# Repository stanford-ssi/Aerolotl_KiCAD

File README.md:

# Aerolotl_KiCAD, make sure to only one person works on it at a time

## Boards in this repo

- Aerolotl SRAD flight computer: the KiCad project at the top level.
- [Battery PCB](BatteryPCB/README.md): the AV bay battery, arming and camera board, with its ordering BOM and Gerbers in `BatteryPCB/fab/`.

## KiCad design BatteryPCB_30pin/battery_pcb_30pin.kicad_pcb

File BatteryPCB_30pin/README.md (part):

# Battery PCB, 30-pin ESP32 version — AV bay power, arming and camera board

> **This folder is a copy of [`../BatteryPCB`](../BatteryPCB) made on 11 Oct 2026 for a 30-pin ESP32 DevKit V1**
> (DOIT layout, ESP-WROOM-32, 2 × 15 pins, rows 25.4 mm apart) instead of the 38-pin ESP32-DevKitC. Only the ESP32
> sockets and what connects to them changed: J1/J2 are 1×15 with pin 1 exactly where the DevKitC's was, the six used
> pins (5 V, GND, GPIO34, GPIO17, GPIO16, GPIO2) are re-routed, R7/R8 and C9/C10 moved next to their new pins,
> and the silk and antenna keep-out follow the new board. Same GPIOs, so the firmware is unchanged.
> See [`LAYOUT_NOTES.md`](LAYOUT_NOTES.md), "30-pin version".

The battery board for the SSI IREC AV bay: it holds the cells for both flight computers
(each with its own pin-switch arming plug) and a 2S pack that powers an ESP32 and a
RunCam Split 4 camera on the back. Formerly called CamControl.

Open `battery_pcb_30pin.kicad_pro` in KiCad 10. The board is a 5.72 in (145.3 mm) round, 2-layer disc
for the AV bay, placed and fully routed.

**Status (30-pin version, 11 Oct 2026):** ERC 0 errors · DRC 0 violations (warnings included) under the strict rules below, with full schematic parity
(3 documented exclusions, as on `BatteryPCB`; checked with KiCad 10.0.6, see `battery_pcb_30pin.kicad_dru`) · `tools/layoutA/verify_A.py` ALL PASS (36 checks; its cut-out check now counts the 7 rim
notches and Koichi's 4 square zip-tie cut-outs). Ready to order: see [Ordering](#ordering).
[`LAYOUT_NOTES.md`](LAYOUT_NOTES.md) has the history of every layout decision.

---

## What's on it

| Block | Parts |
|---|---|
| 2S pack for camera + ESP32 | BT1, BT2 in series → 7.4 V nom / 8.4 V max |
| Input protection | F1 2 A polyfuse → SW1 (camera power switch plug) → Q1 AO3407A reverse-polarity PMOS (gate to GND, ~0.05 V drop) → D1 SMBJ12A TVS |
| Buck 8.4 V → 5.0 V | U1 LMR51430 (500 kHz) + L1 6.8 µH + FB divider; input caps C1 100 nF (at U1's pins) + C2, C11 10 µF |
| Low-battery cut-off | R9 402k / R10 100k on U1's EN: on above 6.2 V, off below 5.4 V at VIN (about 2.7 V per cell), so the 2S pack is never run flat |
| 30-pin ESP32 DevKit V1 socket | J1, J2 — 2 × 1×15 female headers |
| Camera harness | J3 — JST GH 5-pin (+5V, GND, RX, TX, VIDEO), on the back |
| Camera mount | H7–H10 — four M2 × 5 mm SMT standoffs on a 25.5 mm square, on the back |
| Status LED | R6 + D2 on GPIO2 |
| Pack voltage telemetry | R4 100k / R5 39k divider + C8 → GPIO34 (`VBAT_SENSE = VIN × 39/139`, ≤ 2.36 V) |
| Test points | 2 mm through-hole pads, open on both sides. **Right-edge block** (front, between the right rod and the lower zip-tie cut-out, top row / bottom row): TP1 +5V / TP3 GND, TP5 COTS cell + / TP6 COTS cell −, TP7 SRAD cell + / TP8 SRAD cell −. **Lower left** by the camera switch: TP2 VBAT+ (2S pack, before the fuse) / TP4 GND |
| COTS supply | BT3 → SW2 (COTS pin switch plug) → J5 XT30 to the TeleMetrum |
| SRAD supply | BT4 → SW3 (SRAD pin switch plug) → J6 XT30 to the Aerolotl |

Harness connectors are latching Molex Micro-Fit 3.0 for the switch leads (SW1–SW3) and JST GH for the
camera (J3). The two battery outputs, J5 and J6, are **AMASS XT30** (male XT30UPB-M on the board):
**pin 1 is minus, pin 2 is plus**, as moulded on the housing and printed beside each one. The cables take an
XT30U-F female plug. The footprint retains its legacy XT30UPB-F name; order XT30UPB-M (C428721). XT30 holds by friction, so tape or tie the plugs for flight. The male pins are exposed and plus is live when its arming switch closes; keep the mating plug connected or cover the pins when armed.

---

## Three design decisions worth knowing

### 1. The Split 4 has no GPIO shutter line

Its harness is **VCC / GND / Video**. Recording start/stop is done over **UART**
using the RunCam Device Protocol on the TX/RX pads, not a single logic pin.

So the schematic wires **UART2** (GPIO17 TX, GPIO16 RX) to the camera through
series resistors: R7 100 Ω on the ESP32's TX, R8 1 kΩ on the camera's TX (so a 5 V camera
output can't push more than about 1 mA into GPIO16). UART0 is left free so you can still
program and debug over USB. On the original DOIT DevKit V1 design, VIN is fed from USB through an SS14 Schottky, so
USB and this board's 5 V can be connected at the same time. Clones vary: until you have checked yours (USB only:
VIN should read about 4.6–4.8 V, one diode drop below USB), switch the camera pack off before plugging USB in.

The camera connects to this board through the 5-pin J3 harness only (no
button-pad wiring).

**The camera harness is a straight cable.** The Split 4 has five solder pads, in this order with Side B
facing you: RX, TX, Video, GND, VCC. J3 is in the same order (pin 5 … pin 1), so each wire goes straight across,
no crossing (J3's pins 3 and 5 were swapped on 11 Oct 2026 to make this so):

| J3 pin | Net | Camera pad |
|---|---|---|
| 1 | +5V | VCC |
| 2 | GND | GND |
| 3 | VIDEO | Video, or leave unconnected (nothing on this board uses it) |
| 4 | CAM_TX (to ESP32 RX through R8) | TX |
| 5 | CAM_RX (ESP32 TX through R7) | RX |

Note: the original `BatteryPCB` still has the old order (3 = RX, 5 = Video), so its harness is wired by label.

### 2. Everything runs off one 5 V buck

The camera accepts 5–20 V, so 2S could feed it directly — but RunCam explicitly
warns to power it from a regulator rather than a raw battery bus.

Feeding the ESP32 8.4 V directly would also be a problem: the devkit's onboard
AMS1117 would drop 8.4 → 3.3 V and burn about **1.3 W** in a SOT-223. It would
run very hot.

One LMR51430 at 5 V solves both. The ESP32's regulator then only drops 5 → 3.3 V,
and the camera gets a clean supply.

Feedback divider: `Vout = 0.6 × (1 + 100k / 13k) = 5.22 V` (5.05–5.39 V worst case over resistor and reference tolerance, so the camera always sees ≥ 5.0 V)

### 3. COTS and SRAD grounds are deliberately isolated

`COTS_BAT-` and `SRAD_BAT-` are **not** tied to `GND`.

DTEG §6.9.1 requires completely independent recovery systems — separate power
supplies included. Tying the returns together would create a shared failure path
and defeat that. Each of those two cells is its own island: own cell, own switch,
own two-wire output.

Do not "clean this up" by merging the grounds.

---

## Which ESP32

A **30-pin ESP32 DevKit V1** with the DOIT pinout and a WROOM module (the team's USB-C / CP2102 board is one): 2 × 15 pins,
rows 1.0 in (25.4 mm) apart, header order EN, VP, VN, D34 … D13, GND, VIN on one side and D23, D22, TX0 … D15, GND, 3V3 on
the other (antenna at the top). The sockets are wired to that order pin for pin.

- **Check the row spacing before you solder the sockets:** 25.4 mm between the centres of two facing pins. A few narrow
  clones are 22.9 mm; they won't fit.
- **Not a WROVER module:** it uses GPIO16/17 for its PSRAM, and this board uses them for the camera UART.
- **Not the 38-pin ESP32-DevKitC:** that one needs `../BatteryPCB` (2 × 19 sockets).
- It plugs in from the **back**, components facing away from this board, antenna end toward the top: **EN** and **D23**
  go at the "ANTENNA END" silkscreen, **VIN** and **3V3** at the USB end (both labelled on the back silk).
- The board sits inside the area the DevKitC used (51.3 × 28 mm vs 54.3 × 27.9 mm), so nothing new is in its way. Its
  module doesn't overhang: the antenna ends about 5.4 mm past pin 1, about 1.9 mm further in than the DevKitC's.
- **Antenna clearance.** Espressif recommends at least 15 mm of clearance in every direction around the module's PCB
  antenna. The devkit hangs about 13.4 mm under this board, so the back copper has a keep-out (no pour, tracks or vias)
  15 mm to each side of the antenna and past its end, outlined on the back silk (extended 1.9 mm toward the centre for
  this board's antenna). Everything on the front, cells and pin-switch stack included, is at least 15 mm away through
  the board. **Use a nylon M3 bolt and nut in H5**: it is the pin-switch stack bolt right over the antenna.
  [Espressif: positioning a module on a base board](https://docs.espressif.com/projects/esp-hardware-design-guidelines/en/latest/esp32/pcb-layout-design.html#general-principles-of-pcb-layout-for-modules-positioning-a-module-on-a-base-board)
- The AVBay1 Onshape model already shows a 2 × 15 DevKit, which matches this version.

## ESP32 pin map

| Function | Pin | Net |
|---|---|---|
| 5 V in | J1-15 (VIN) | `+5V` |
| GND | J1-14, J2-14 | `GND` |
| Camera UART TX | J2-9 (TX2, GPIO17) | `ESP_TX2` → R7 → `CAM_RX` |
| Camera UART RX | J2-10 (RX2, GPIO16) | `ESP_RX2` → R8 → `CAM_TX` |
| Status LED | J2-12 (D2, GPIO2) | `LED_GPIO` → R6 → D2 |
| Pack voltage | J1-4 (D34, GPIO34, ADC1) | `VBAT_SENSE` |

J1 is the devkit's EN … VIN header and J2 its D23 … 3V3 header,
both counted from the **antenna end**, which faces the top of the board. Same GPIOs as the DevKitC version.

Every unused header pin is broken out to a named net (`L06_IO35`, `R09_IO18`, …)
so you can see what's free. Those produce 24 `isolated_pin_label` ERC warnings —
expected and harmless, they're spare breakouts by design.

The 30-pin board doesn't break out GPIO6–11 (the module's SPI flash) or GPIO0. Of the strapping pins it does break out,
keep GPIO12 (`L12_IO12`) low at boot; GPIO2 (the LED, pulled low through R6/D2) and GPIO15 are fine as wired.

---

## Camera mounting

The RunCam Split 4 board (29 × 29 mm, M2 holes on a 25.5 mm square) sits on four Würth
9774050243R M2 × 5 mm SMT standoffs (H7–H10) on the back of this board, next to its J3 harness.
Each standoff has a 1.4 mm locating pin on its base that drops into a 3.0 mm hole in the board (Würth's land pattern);
the pin stays inside the 1.6 mm board, so nothing reaches the battery side. Use M2 screws 4–6 mm long.
`battery_pcb.pretty/RunCam_Split4_OnStandoffs.kicad_mod` places its 3D outline; it has no pads
and is excluded from the BOM.

Source: [RunCam Split 4 manual](https://www.runcam.com/download/split4k/RC_Split_4k_Manual_EN.pdf)

---

## Open items

1. **The ESP32's Bluetooth is a 2.4 GHz transmitter.** DTEG §4.3.5 forbids
   powering transmitting electronics in the pit area without authorization, and
   2.4 GHz is not in ESRA's Student Band Plan. SW1 exists partly so you can keep
   it off until the pad. Declare this radio in your progress reports.
2. **No SD card module** is on this schematic — you mentioned one for the plate
   but didn't list it in the brief. Easy to add on SPI (GPIO5/18/19/23).
3. **Confirm the camera's logic level** before connecting RX/TX: power the camera and
   measure its TX pad to GND. About 3.3 V: wire it straight on. About 5 V: R8 (1 kΩ)
   protects the ESP32's input, but the camera may not read the ESP32's 3.3 V TX; add a
   level shifter then.

Layout-specific items are in [`LAYOUT_NOTES.md`](LAYOUT_NOTES.md).

---

## Mechanical dimensions

Front view (battery side), origin at the board centre, **x right, y up toward the pin-switch stack** (the Onshape frame).
All in mm unless noted.

| Feature | Size | Position |
|---|---|---|
| Board | Ø 145.29 (5.720 in), 1.6 thick FR-4 | centred |
| Rod holes H1/H2 (3/8 in threaded rod) | Ø 10.32 (13/32 in) | (−60, 0), (60, 0): 120 apart |
| Rod washer keep-out (no copper, both faces) | Ø 21.2 | around H1/H2 |
| TeleMetrum sled screw holes H3/H4 (M4) | Ø 4.5 | (−8.7, −50), (8.7, −50): 17.4 apart |
| Sled screw keep-out (no copper) | Ø 9.6 | around H3/H4 |
| Pin-switch stack bolt holes H5/H6 (M3) | Ø 3.2 | (18.5, 41.88), (−18.5, 48.88) |
| Pin-switch stack footprint (silk outline) | 45 wide, from y 36.88 out to the pin faces at 68.88 | x −22.5 … 22.5 |
| Camera standoffs H7–H10 (back, Würth M2 × 5 mm SMT) | 25.5 square | centre (−35.5, 30): upper left, near the rim |
| Battery holders BT1–BT4 (Keystone 1042) | 14.9 tall | centres x −36.5, −14.3, 11.1, 36.5; y −2.25 |
| ESP32 sockets J1/J2 (back, 1×15, 8.5 tall) | columns 25.4 apart | x 23.8 and −1.6; pin 1 at y 35.12, pin 15 at y −0.44 |
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
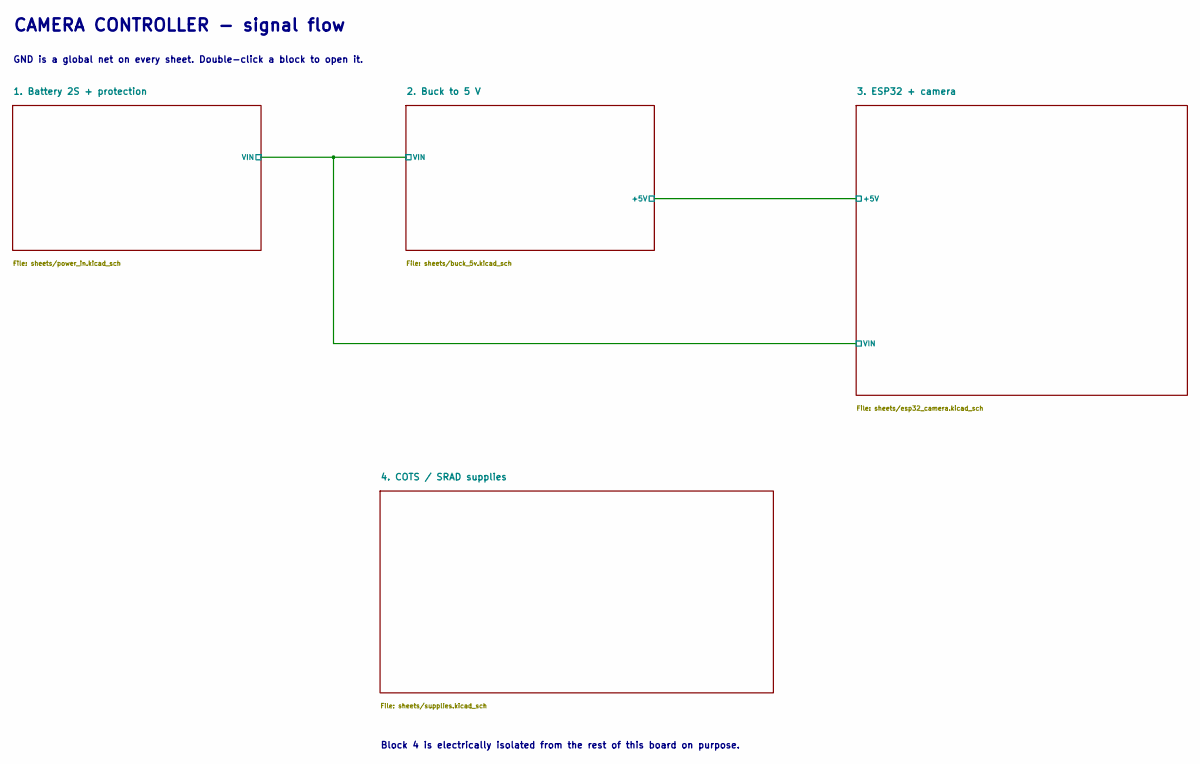
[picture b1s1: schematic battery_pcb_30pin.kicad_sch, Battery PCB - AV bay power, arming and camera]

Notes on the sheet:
CAMERA CONTROLLER - signal flow
GND is a global net on every sheet. Double-click a block to open it.
Block 4 is electrically isolated from the rest of this board on purpose.

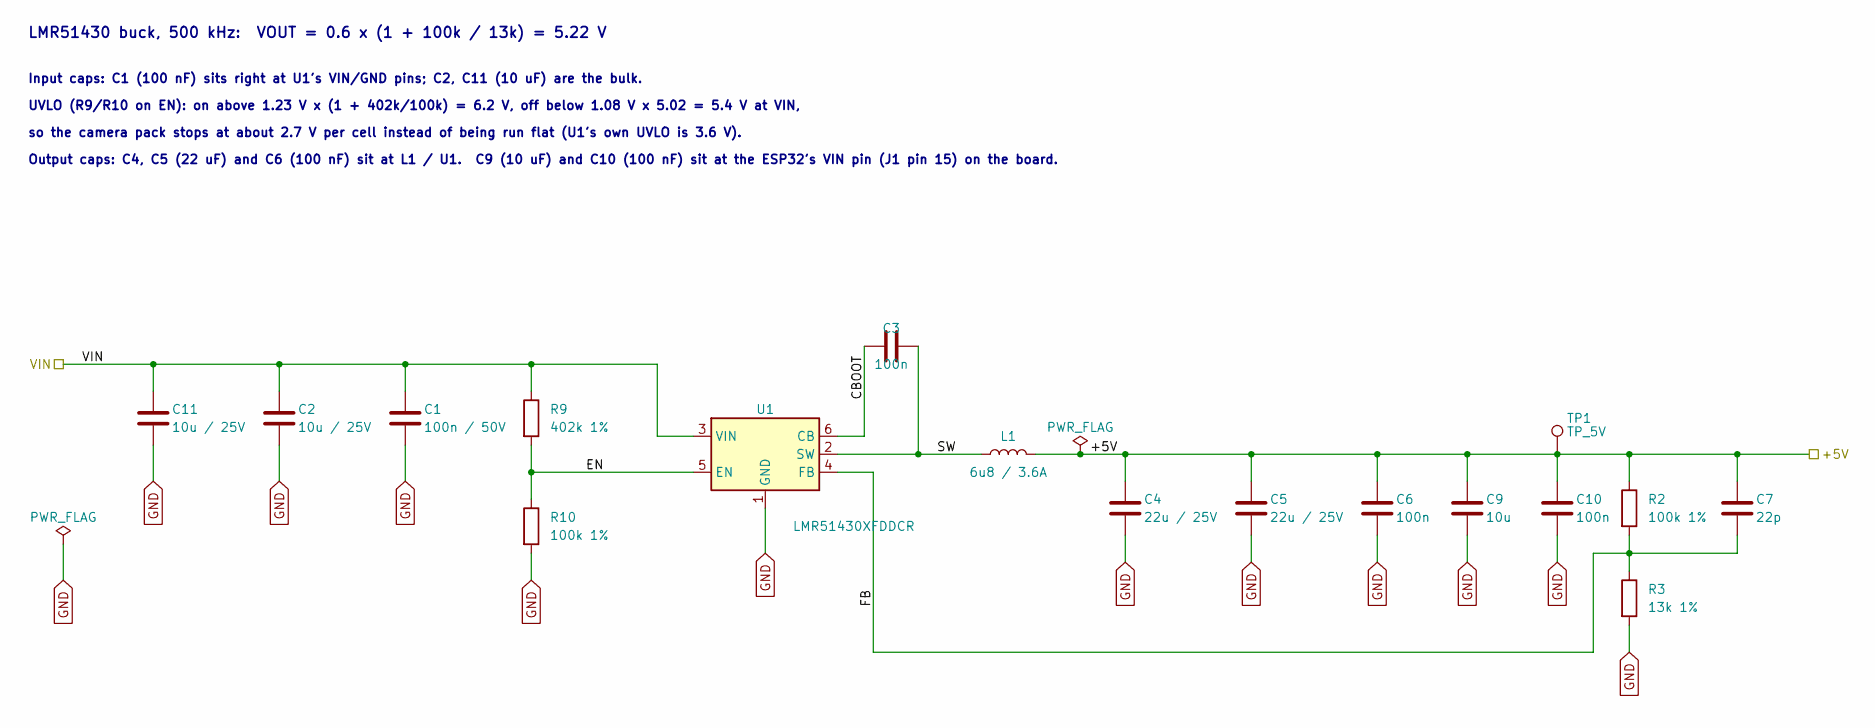
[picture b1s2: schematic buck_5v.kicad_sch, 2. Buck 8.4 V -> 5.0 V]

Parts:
C1: 100n / 50V; C_0805_2012Metric; MPN CC0805KRX7R9BB104; LCSC C49678
C2, C11: 10u / 25V; C_0805_2012Metric; MPN CL21A106KAYNNNE
C3, C6, C10: 100n; C_0603_1608Metric; MPN CL10B104KB8NNNC
C4, C5: 22u / 25V; C_0805_2012Metric; MPN CL21A226MAQNNNE; LCSC C45783
C7: 22p; C_0603_1608Metric; MPN CL10C220JB8NNNC
C9: 10u; C_0805_2012Metric; MPN CL21A106KAYNNNE
L1: 6u8 / 3.6A; L_Bourns_SRN6045TA; MPN SRN6045TA-6R8M
R2, R10: 100k 1%; R_0603_1608Metric; MPN RC0603FR-07100KL
R3: 13k 1%; R_0603_1608Metric; MPN RC0603FR-0713KL
R9: 402k 1%; R_0603_1608Metric; MPN RC0603FR-07402KL
TP1: TP_5V; TestPoint_THTPad_D2.0mm_Drill1.0mm
U1: LMR51430XFDDCR; SOT-23-6; MPN LMR51430XFDDCR

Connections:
/1. Battery 2S + protection/VIN: C1.1, C2.1, C11.1, R9.1, U1.3 (VIN); also elsewhere on the board
/2. Buck to 5 V/+5V: C4.1, C5.1, C6.1, C7.1, C9.1, C10.1, L1.2, R2.1, TP1.1 (1_1); also elsewhere on the board
/2. Buck to 5 V/CBOOT: C3.1, U1.6 (CB)
/2. Buck to 5 V/EN: R9.2, R10.1, U1.5 (EN)
/2. Buck to 5 V/FB: C7.2, R2.2, R3.1, U1.4 (FB)
/2. Buck to 5 V/SW: C3.2, L1.1, U1.2 (SW)
GND: C1.2, C2.2, C4.2, C5.2, C6.2, C9.2, C10.2, C11.2, R3.2, R10.2, U1.1 (GND); also elsewhere on the board

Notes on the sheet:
UVLO (R9/R10 on EN): on above 1.23 V x (1 + 402k/100k) = 6.2 V, off below 1.08 V x 5.02 = 5.4 V at VIN,
LMR51430 buck, 500 kHz: VOUT = 0.6 x (1 + 100k / 13k) = 5.22 V
Output caps: C4, C5 (22 uF) and C6 (100 nF) sit at L1 / U1. C9 (10 uF) and C10 (100 nF) sit at the ESP32's VIN pin (J1 pin 15) on the board.
so the camera pack stops at about 2.7 V per cell instead of being run flat (U1's own UVLO is 3.6 V).
Input caps: C1 (100 nF) sits right at U1's VIN/GND pins; C2, C11 (10 uF) are the bulk.

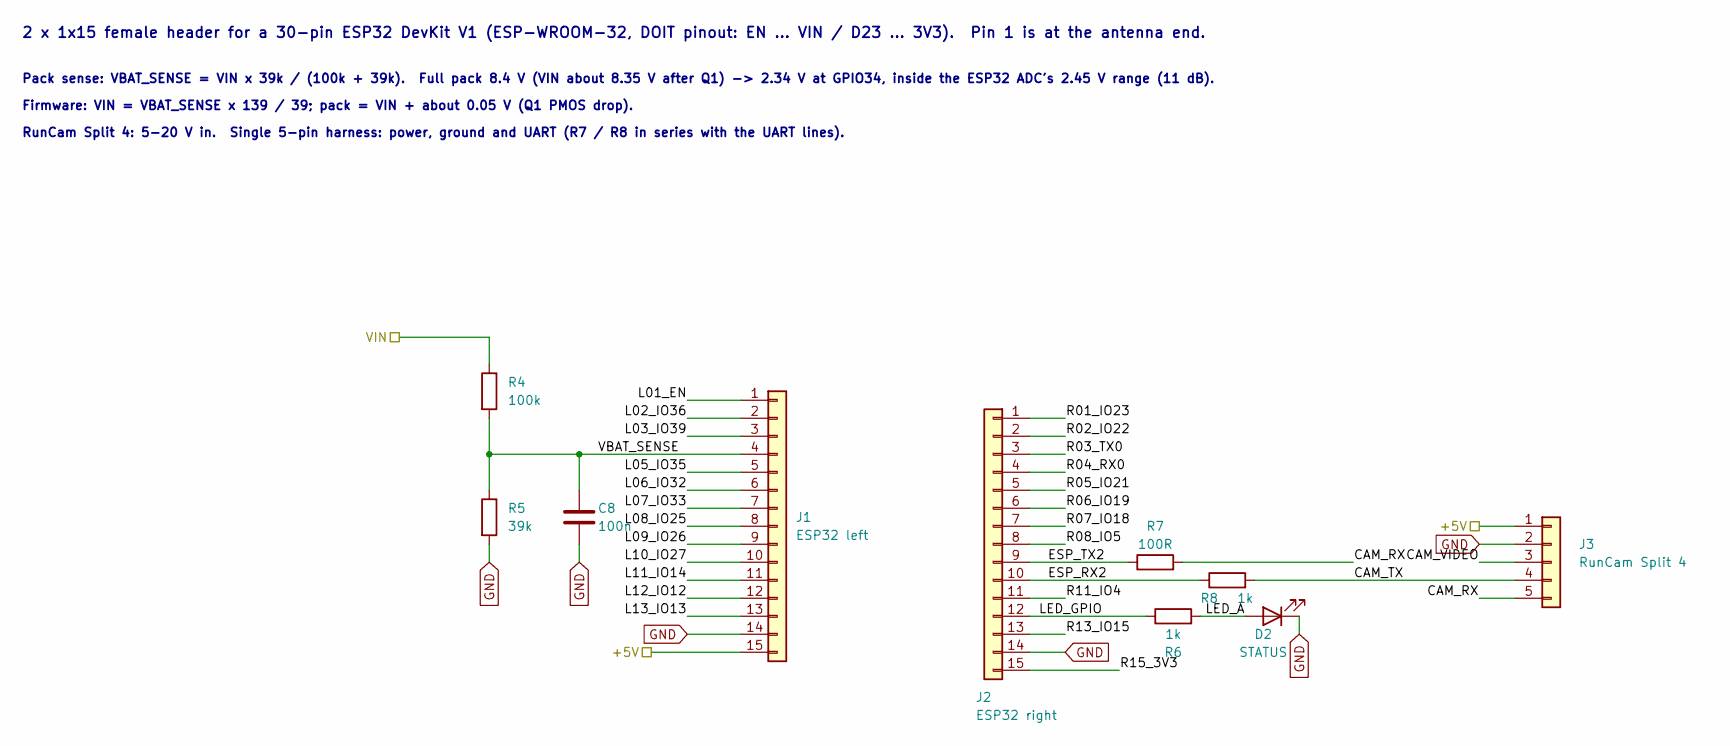
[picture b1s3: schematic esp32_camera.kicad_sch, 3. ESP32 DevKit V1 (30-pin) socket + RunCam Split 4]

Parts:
C8: 100n; C_0603_1608Metric; MPN CL10B104KB8NNNC
D2: STATUS; LED_0805_2012Metric; MPN NCD0805R1; LCSC C84256
J1: ESP32 left; PinSocket_1x15_P2.54mm_Vertical; MPN PPTC151LFBN-RC
J2: ESP32 right; PinSocket_1x15_P2.54mm_Vertical; MPN PPTC151LFBN-RC
J3: RunCam Split 4; JST_GH_BM05B-GHS-TBT_1x05-1MP_P1.25mm_Vertical; MPN BM05B-GHS-TBT
R4: 100k; R_0603_1608Metric; MPN RC0603FR-07100KL
R5: 39k; R_0603_1608Metric; MPN RC0603FR-0739KL
R6, R8: 1k; R_0603_1608Metric; MPN RC0603FR-071KL
R7: 100R; R_0603_1608Metric; MPN RC0603FR-07100RL

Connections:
/1. Battery 2S + protection/VIN: R4.1; also elsewhere on the board
/2. Buck to 5 V/+5V: J1.15, J3.1; also elsewhere on the board
/3. ESP32 + camera/CAM_RX: J3.5, R7.2
/3. ESP32 + camera/CAM_TX: J3.4, R8.2
/3. ESP32 + camera/CAM_VIDEO: J3.3
/3. ESP32 + camera/ESP_RX2: J2.10, R8.1
/3. ESP32 + camera/ESP_TX2: J2.9, R7.1
/3. ESP32 + camera/L01_EN: J1.1
/3. ESP32 + camera/L02_IO36: J1.2
/3. ESP32 + camera/L03_IO39: J1.3
/3. ESP32 + camera/L05_IO35: J1.5
/3. ESP32 + camera/L06_IO32: J1.6
/3. ESP32 + camera/L07_IO33: J1.7
/3. ESP32 + camera/L08_IO25: J1.8
/3. ESP32 + camera/L09_IO26: J1.9
/3. ESP32 + camera/L10_IO27: J1.10
/3. ESP32 + camera/L11_IO14: J1.11
/3. ESP32 + camera/L12_IO12: J1.12
/3. ESP32 + camera/L13_IO13: J1.13
/3. ESP32 + camera/LED_A: D2.2 (A), R6.2
/3. ESP32 + camera/LED_GPIO: J2.12, R6.1
/3. ESP32 + camera/R01_IO23: J2.1
/3. ESP32 + camera/R02_IO22: J2.2
/3. ESP32 + camera/R03_TX0: J2.3
/3. ESP32 + camera/R04_RX0: J2.4
/3. ESP32 + camera/R05_IO21: J2.5
/3. ESP32 + camera/R06_IO19: J2.6
/3. ESP32 + camera/R07_IO18: J2.7
/3. ESP32 + camera/R08_IO5: J2.8
/3. ESP32 + camera/R11_IO4: J2.11
/3. ESP32 + camera/R13_IO15: J2.13
/3. ESP32 + camera/R15_3V3: J2.15
/3. ESP32 + camera/VBAT_SENSE: C8.1, J1.4, R4.2, R5.1
GND: C8.2, D2.1 (K), J1.14, J2.14, J3.2, R5.2; also elsewhere on the board

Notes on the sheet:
Firmware: VIN = VBAT_SENSE x 139 / 39; pack = VIN + about 0.05 V (Q1 PMOS drop).
RunCam Split 4: 5-20 V in. Single 5-pin harness: power, ground and UART (R7 / R8 in series with the UART lines).
Pack sense: VBAT_SENSE = VIN x 39k / (100k + 39k). Full pack 8.4 V (VIN about 8.35 V after Q1) -> 2.34 V at GPIO34, inside the ESP32 ADC's 2.45 V range (11 dB).
2 x 1x15 female header for a 30-pin ESP32 DevKit V1 (ESP-WROOM-32, DOIT pinout: EN ... VIN / D23 ... 3V3). Pin 1 is at the antenna end.

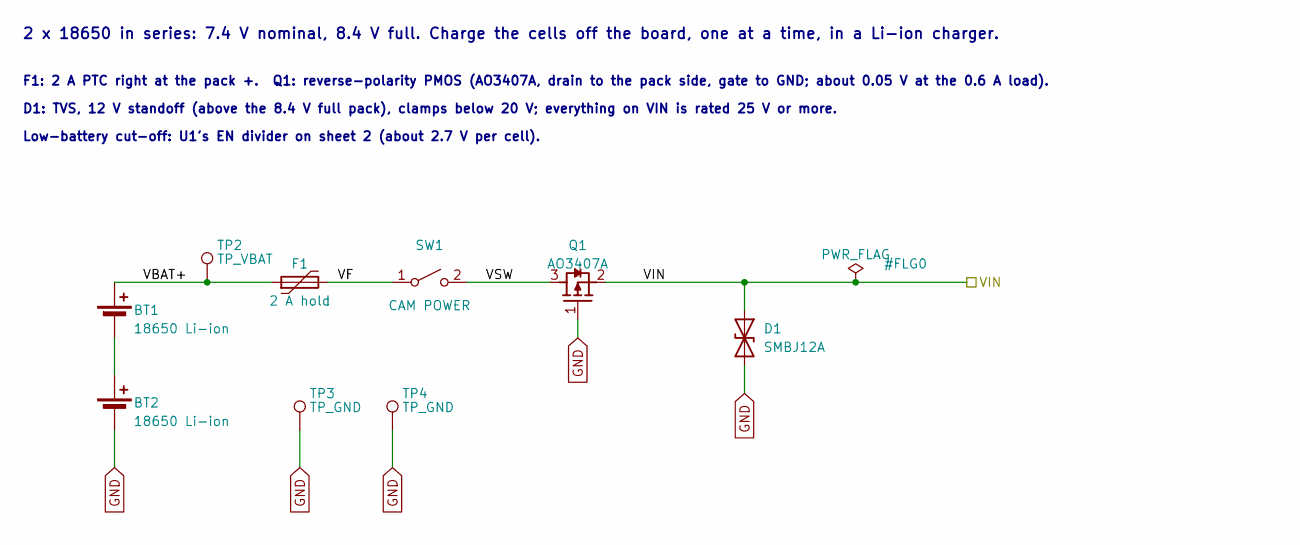
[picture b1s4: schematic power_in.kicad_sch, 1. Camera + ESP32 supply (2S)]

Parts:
BT1, BT2: 18650 Li-ion; BatteryHolder_Keystone_1042_1x18650; MPN 1042
D1: SMBJ12A; D_SMB; MPN SMBJ12A
F1: 2 A hold; Fuse_1812_4532Metric; MPN 1812L200/12DR
Q1: AO3407A; SOT-23-3; MPN AO3407A
SW1: CAM POWER; Molex_Micro-Fit_3.0_43650-0215_1x02_P3.00mm_Vertical; MPN 0436500215
TP2: TP_VBAT; TestPoint_THTPad_D2.0mm_Drill1.0mm
TP3, TP4: TP_GND; TestPoint_THTPad_D2.0mm_Drill1.0mm

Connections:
/1. Battery 2S + protection/VBAT+: BT1.1 (+), F1.1, TP2.1 (1_1)
/1. Battery 2S + protection/VF: F1.2, SW1.1 (A)
/1. Battery 2S + protection/VIN: D1.1 (A1), Q1.2 (S); also elsewhere on the board
/1. Battery 2S + protection/VSW: Q1.3 (D), SW1.2 (B)
GND: BT2.2 (-), D1.2 (A2), Q1.1 (G), TP3.1 (1_1), TP4.1 (1_1); also elsewhere on the board
unnamed: BT1.2 (-), BT2.1 (+)

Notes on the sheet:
2 x 18650 in series: 7.4 V nominal, 8.4 V full. Charge the cells off the board, one at a time, in a Li-ion charger.
Low-battery cut-off: U1's EN divider on sheet 2 (about 2.7 V per cell).
D1: TVS, 12 V standoff (above the 8.4 V full pack), clamps below 20 V; everything on VIN is rated 25 V or more.
F1: 2 A PTC right at the pack +. Q1: reverse-polarity PMOS (AO3407A, drain to the pack side, gate to GND; about 0.05 V at the 0.6 A load).

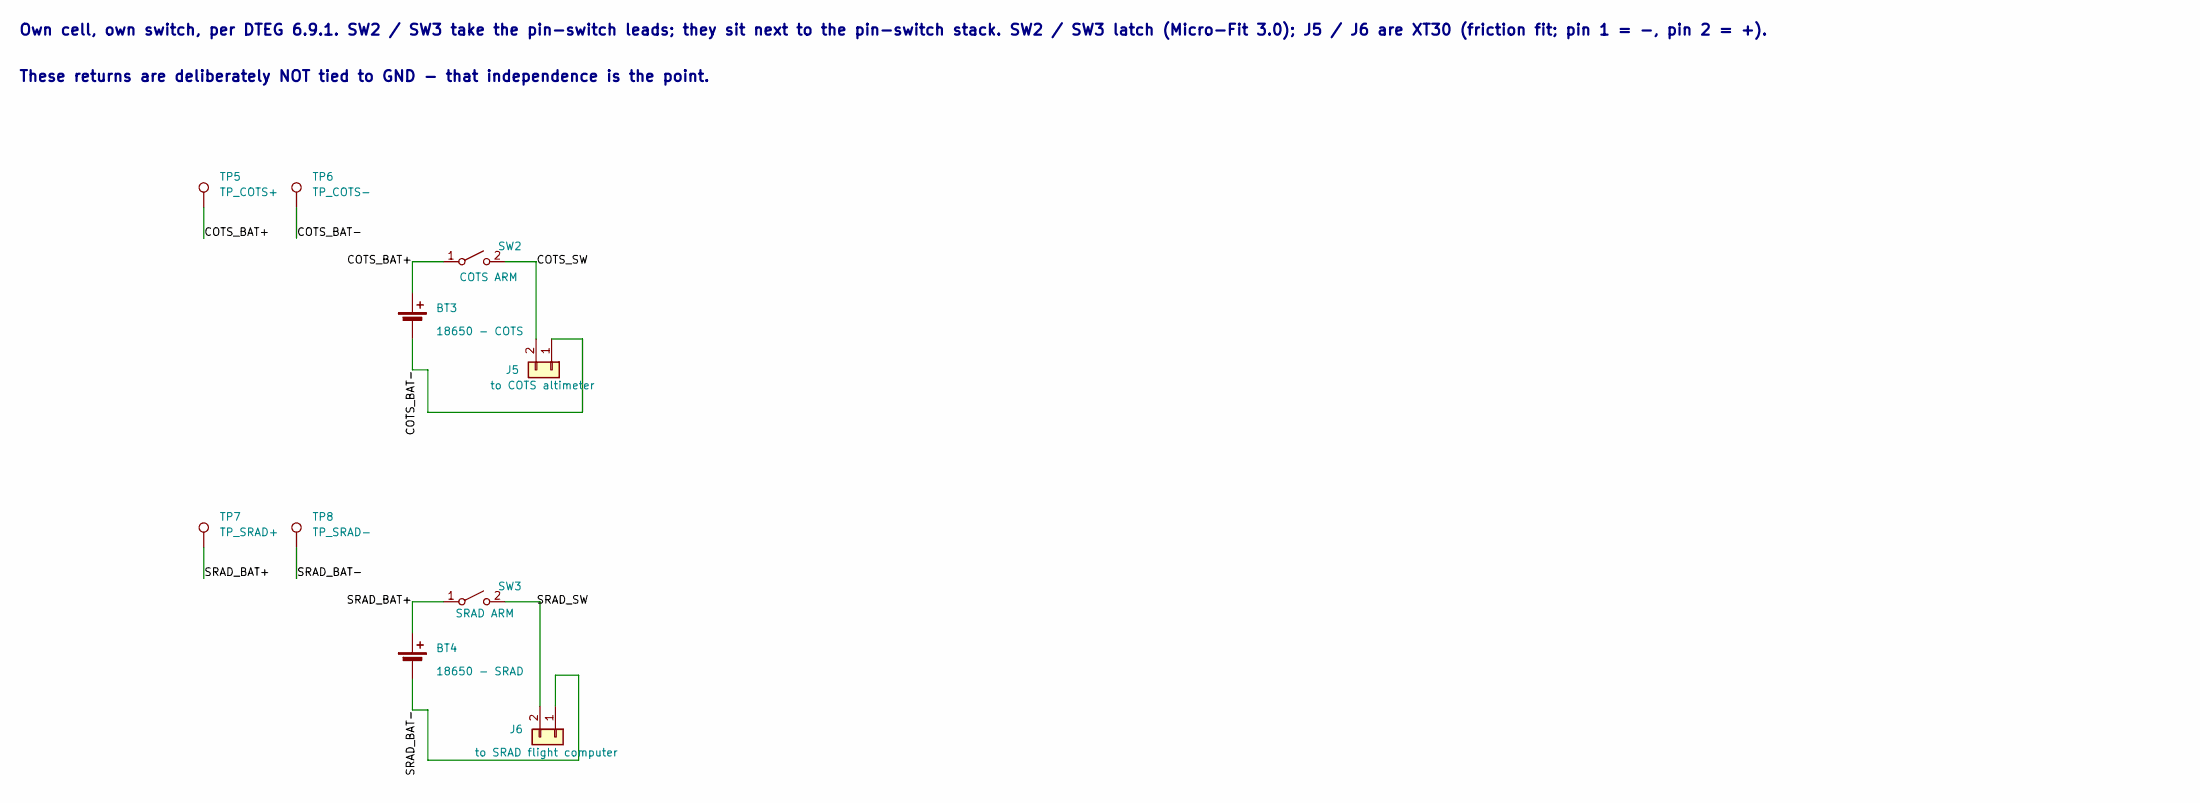
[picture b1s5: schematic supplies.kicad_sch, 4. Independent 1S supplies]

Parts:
BT3: 18650 - COTS; BatteryHolder_Keystone_1042_1x18650; MPN 1042
BT4: 18650 - SRAD; BatteryHolder_Keystone_1042_1x18650; MPN 1042
J5: to COTS altimeter; AMASS_XT30UPB-F_1x02_P5.0mm_Vertical; MPN XT30UPB-M
J6: to SRAD flight computer; AMASS_XT30UPB-F_1x02_P5.0mm_Vertical; MPN XT30UPB-M
SW2: COTS ARM; Molex_Micro-Fit_3.0_43650-0215_1x02_P3.00mm_Vertical; MPN 0436500215
SW3: SRAD ARM; Molex_Micro-Fit_3.0_43650-0215_1x02_P3.00mm_Vertical; MPN 0436500215
TP5: TP_COTS+; TestPoint_THTPad_D2.0mm_Drill1.0mm
TP6: TP_COTS-; TestPoint_THTPad_D2.0mm_Drill1.0mm
TP7: TP_SRAD+; TestPoint_THTPad_D2.0mm_Drill1.0mm
TP8: TP_SRAD-; TestPoint_THTPad_D2.0mm_Drill1.0mm

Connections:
/4. COTS / SRAD supplies/COTS_BAT+: BT3.1 (+), SW2.1 (A), TP5.1
/4. COTS / SRAD supplies/COTS_BAT-: BT3.2 (-), J5.1, TP6.1
/4. COTS / SRAD supplies/COTS_SW: J5.2, SW2.2 (B)
/4. COTS / SRAD supplies/SRAD_BAT+: BT4.1 (+), SW3.1 (A), TP7.1
/4. COTS / SRAD supplies/SRAD_BAT-: BT4.2 (-), J6.1, TP8.1
/4. COTS / SRAD supplies/SRAD_SW: J6.2, SW3.2 (B)

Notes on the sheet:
Own cell, own switch, per DTEG 6.9.1. SW2 / SW3 take the pin-switch leads; they sit next to the pin-switch stack. SW2 / SW3 latch (Micro-Fit 3.0); J5 / J6 are XT30 (friction fit; pin 1 = -, pin 2 = +).
These returns are deliberately NOT tied to GND - that independence is the point.

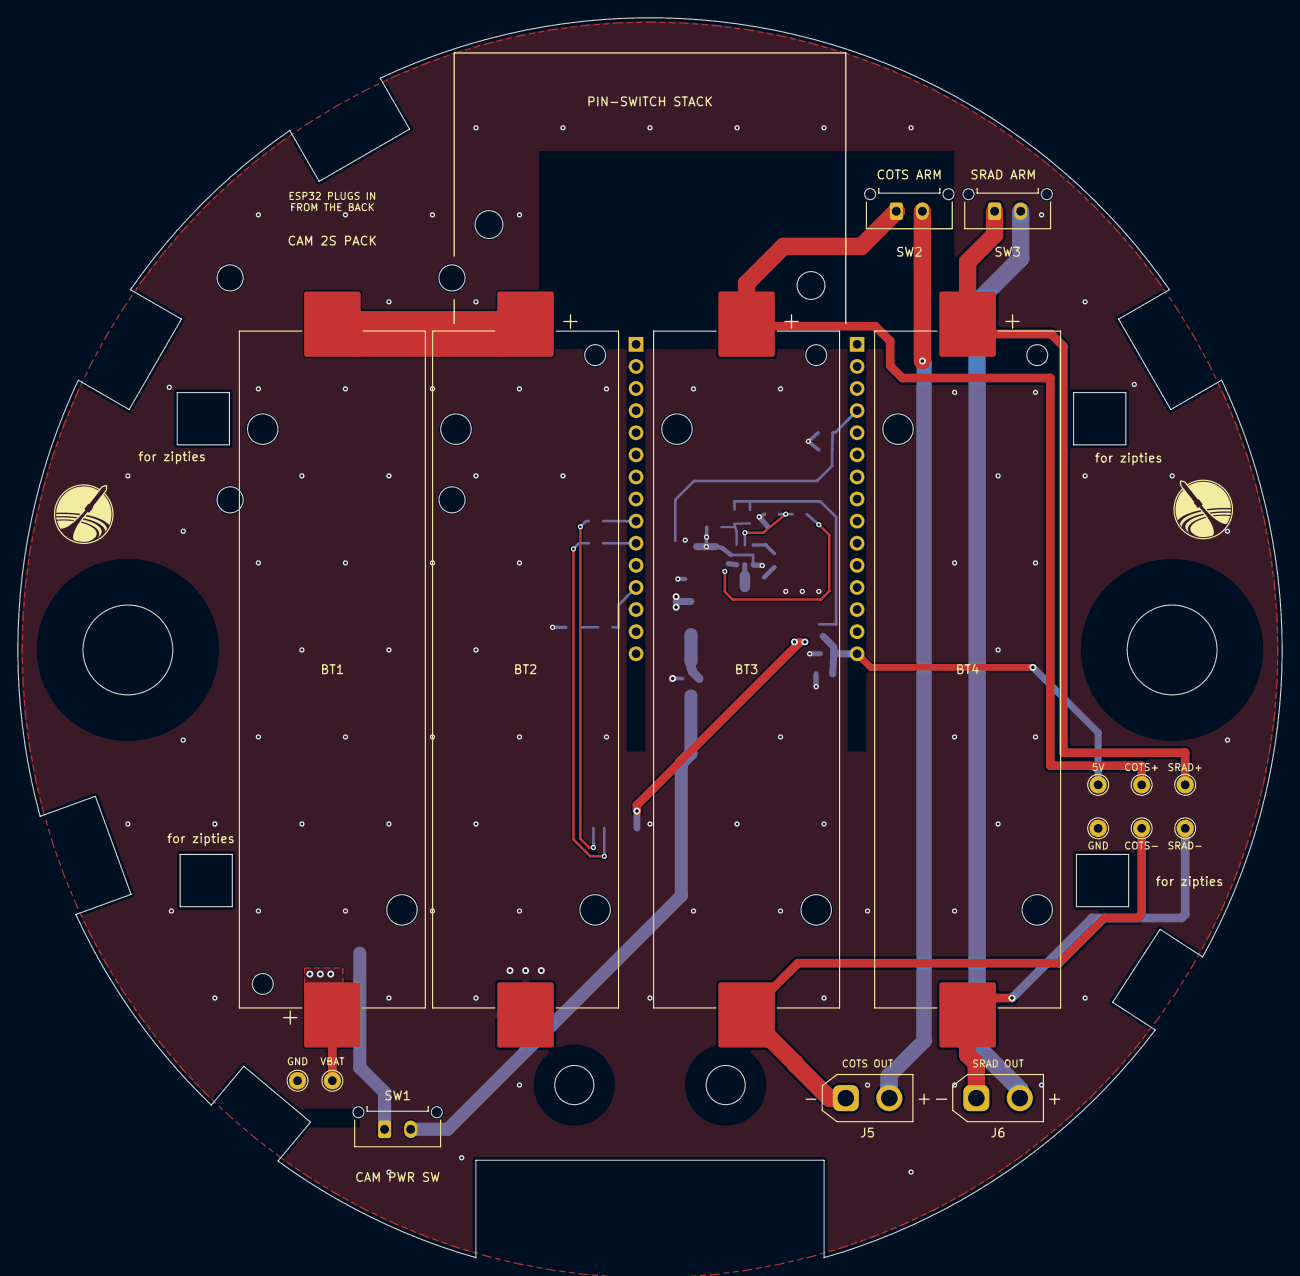
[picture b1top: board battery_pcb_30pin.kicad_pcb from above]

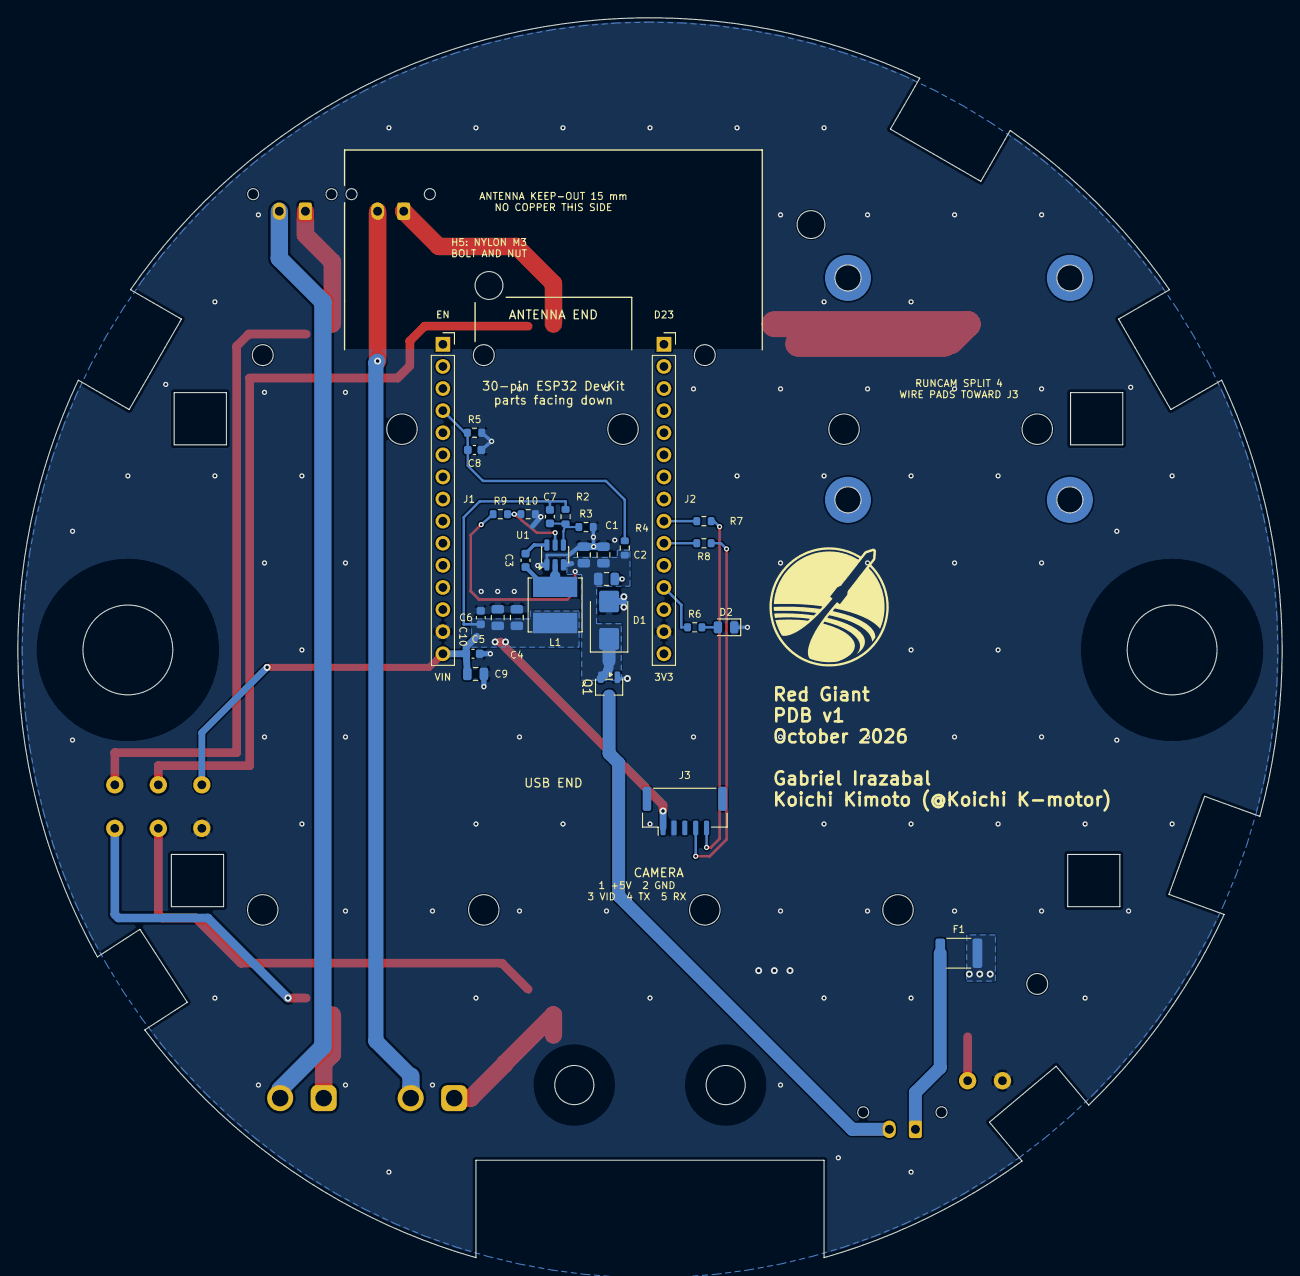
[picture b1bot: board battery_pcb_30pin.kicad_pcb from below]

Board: 2 copper layers, 145.3 x 142.5 mm, 57 parts (34 on the bottom side), 24 nets.

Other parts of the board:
CAM1: RunCam Split 4 (on standoffs); RunCam_Split4_OnStandoffs
H1, H2: 3/8 rod; MountingHole_10.3mm_3-8in_Rod
H3: TeleMetrum sled M4; MountingHole_4.5mm_TeleMetrum_Sled_L
H4: TeleMetrum sled M4; MountingHole_4.5mm_TeleMetrum_Sled_R
H5, H6: Pin switch stack M3; MountingHole_3.2mm_M3_RoundStandoff_D5
H7, H8, H9, H10: Wurth 9774050243 M2x5 standoff (camera); Mounting_Wuerth_WA-SMSI-M2_H5mm_9774050243

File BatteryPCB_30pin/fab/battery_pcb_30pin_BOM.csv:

Section,Qty per board,Order qty (2 boards + spares),References,Description,Manufacturer,MPN,LCSC #,Other supplier,Footprint,Notes
Board (solder on),4,8,"BT1, BT2, BT3, BT4","Battery holder, 1x 18650, surface mount",Keystone Electronics,1042,,DigiKey 36-1042-ND (not sold by LCSC),BatteryHolder_Keystone_1042_1x18650,
Board (solder on),1,10,C1,"Capacitor 100 nF 50 V X7R, 0805",YAGEO,CC0805KRX7R9BB104,C49678,,C_0805_2012Metric,
Board (solder on),3,11,"C2, C9, C11","Capacitor 10 uF 25 V X5R, 0805",Samsung Electro-Mechanics,CL21A106KAYNNNE,C15850,,C_0805_2012Metric,"Low LCSC stock on 9 Oct 2026 (20 pcs). Alt: Murata GRM21BR61E106KA73L (LCSC C84416) or FH 0805X106K250NT (C40894), same 10 uF 25 V X5R 0805"
Board (solder on),4,13,"C3, C6, C8, C10","Capacitor 100 nF 50 V X7R, 0603",Samsung Electro-Mechanics,CL10B104KB8NNNC,C1591,,C_0603_1608Metric,"Low LCSC stock on 9 Oct 2026 (100 pcs, MOQ 100). Alt: FH 0603B104K500NT (LCSC C30926), same 100 nF 50 V X7R 0603"
Board (solder on),2,10,"C4, C5","Capacitor 22 uF 25 V X5R, 0805",Samsung Electro-Mechanics,CL21A226MAQNNNE,C45783,,C_0805_2012Metric,
Board (solder on),1,10,C7,"Capacitor 22 pF 50 V C0G, 0603",Samsung Electro-Mechanics,CL10C220JB8NNNC,C1653,,C_0603_1608Metric,
Board (solder on),1,3,D1,"TVS diode, 12 V standoff, SMB",Littelfuse,SMBJ12A,C151251,,D_SMB,"LCSC's spec rows for C151251 show 13 V / 21.5 V clamp (SMBJ13A values); the part is SMBJ12A (12 V standoff, 19.9 V clamp). Either is safe here"
Board (solder on),1,10,D2,"LED, red, 0805 (status light, -30 to +85 C)",Foshan NationStar Optoelectronics,NCD0805R1,C84256,,LED_0805_2012Metric,
Board (solder on),1,3,F1,"Resettable fuse (PTC) 2 A hold, 12 V, 1812",Littelfuse,1812L200/12DR,C315901,,Fuse_1812_4532Metric,Alt: Polytronics SMD1812P200TF/16
Board (solder on),2,5,"J1, J2","Female header 1x15, 2.54 mm, 8.5 mm tall (socket for the 30-pin ESP32 DevKit V1)",Sullins Connector Solutions,PPTC151LFBN-RC,C2897378,DigiKey S7013-ND if you want the Sullins part itself,PinSocket_1x15_P2.54mm_Vertical,
Board (solder on),1,3,J3,JST GH 5-pin vertical header (camera),JST,BM05B-GHS-TBT,C189891,,JST_GH_BM05B-GHS-TBT_1x05-1MP_P1.25mm_Vertical,
Board (solder on),2,5,"J5, J6","AMASS XT30 male, vertical PCB mount (battery outputs)",AMASS,XT30UPB-M,C428721,,AMASS_XT30UPB-F_1x02_P5.0mm_Vertical,"J5 to the TeleMetrum, J6 to the Aerolotl. Pin 1 = minus, pin 2 = plus, as marked on the housing"
Board (solder on),1,3,L1,"Power inductor 6.8 uH, 3.6 A rms / 5.7 A sat, 6 x 6 mm",Bourns,SRN6045TA-6R8M,C2041457,,L_Bourns_SRN6045TA,
Board (solder on),1,3,Q1,"P-MOSFET -30 V -4.3 A, SOT-23 (reverse-polarity protection, gate to GND)",Alpha & Omega Semiconductor,AO3407A,C15155,,SOT-23-3,
Board (solder on),3,11,"R2, R4, R10","Resistor 100 k 1%, 0603",Yageo,RC0603FR-07100KL,C14675,,R_0603_1608Metric,
Board (solder on),1,10,R3,"Resistor 13 k 1%, 0603",Yageo,RC0603FR-0713KL,C137796,,R_0603_1608Metric,
Board (solder on),1,10,R5,"Resistor 39 k 1%, 0603",Yageo,RC0603FR-0739KL,C163424,,R_0603_1608Metric,
Board (solder on),2,10,"R6, R8","Resistor 1 k 1%, 0603",Yageo,RC0603FR-071KL,C22548,,R_0603_1608Metric,
Board (solder on),1,10,R7,"Resistor 100 ohm 1%, 0603",Yageo,RC0603FR-07100RL,C105588,,R_0603_1608Metric,
Board (solder on),1,10,R9,"Resistor 402 k 1%, 0603",Yageo,RC0603FR-07402KL,C874662,,R_0603_1608Metric,
Board (solder on),3,7,"SW1, SW2, SW3",Molex Micro-Fit 3.0 2-pin vertical header,Molex,0436500215,C293740,,Molex_Micro-Fit_3.0_43650-0215_1x02_P3.00mm_Vertical,"SW1 camera power, SW2/SW3 pin-switch leads"
Board (solder on),1,3,U1,"Buck converter 4.5-36 V in, 3 A, SOT-23-6 (makes the 5 V rail)",Texas Instruments,LMR51430XFDDCR,C5219260,,SOT-23-6,
Board hardware,4,8,H7-H10,"SMT steel standoff, M2 thread, 5 mm (camera mounts, back side)",Wurth Elektronik,9774050243R,,DigiKey 732-7097-1-ND / Mouser 710-9774050243R (not sold by LCSC),,Soldered like a part
Plugs in / mounts on,1,2,,"ESP32 dev board, 30-pin DevKit V1 (DOIT layout, ESP-WROOM-32)",DOIT (or clone),ESP32 DevKit V1 (30-pin),,Team stock (the USB-C / CP2102 version). Any 30-pin DOIT-layout ESP32 DevKit V1 fits,,"Plugs into J1/J2 from the back, EN / D23 at the ANTENNA END mark. Must be the 30-pin DOIT pinout (EN..VIN / D23..3V3) with 25.4 mm (1.0 in) row spacing and a WROOM module: not a WROVER (GPIO16/17 used), not the 38-pin DevKitC"
Plugs in / mounts on,1,2,,"Camera, RunCam Split 4 V3 (29 x 29 mm, M2 holes on 25.5 mm square, 5-20 V, 450 mA max)",RunCam,Split 4 V3,,,,"Sits on H7-H10. Harness: a straight 5-wire JST GH cable from J3 to the camera's 5 pads (J3 pin 1..5 = VCC, GND, Video, TX, RX; video can be left off)"
Plugs in / mounts on,4,8,,"Screw M2 x 5 mm, pan head",,,,,,Camera to standoffs. 4-6 mm all fit (the M2 screws that come with the camera are fine)
Plugs in / mounts on,4,8,,"18650 Li-ion cell, flat top, high drain",Molicel,INR-18650-P28A,,,,Or any high-drain flat-top 18650; never mix cells in the series pair
Cable side,3,6,"SW1, SW2, SW3","Micro-Fit 3.0 receptacle housing, 2-pin",Molex,0436450200,C114089,,,
Cable side,6,12,"SW1, SW2, SW3","Micro-Fit 3.0 female crimp terminal, 20-24 AWG",Molex,0430300007,C293530,,,"Needs a Micro-Fit crimper, or buy pre-crimped leads"
Cable side,2,4,"J5, J6","XT30 female plug, solder cup (cable to each flight computer)",AMASS,XT30U-F,C99102,,,Solder 18-20 AWG; check polarity against the +/- on the board
Cable side,1,2,J3,"JST GH housing, 5-pin",JST,GHR-05V-S,C160419,,,Or a pre-crimped GH 5-pin cable
Cable side,5,10,J3,"JST GH crimp terminal, 26-30 AWG",JST,SSHL-002T-P0.2,C189897,,,
Cable side,1,2,SW1,"Toggle switch, SPST, 3 A or more, panel mount",,,,,,"Camera power switch, wired to the SW1 plug"
PCB,1,5,,"PCB, 2 layers, 145.3 mm (5.72 in) round, 1.6 mm FR-4, 1 oz copper",JLCPCB (or any fab),,,,,Upload fab/battery_pcb_30pin_gerbers.zip; 5 is the usual minimum order

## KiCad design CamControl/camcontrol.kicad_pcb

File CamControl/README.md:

# Camera Controller — ESP32 + RunCam Split 4

Bluetooth-controlled camera trigger for the SSI IREC av bay, plus switched
power feed-throughs for the COTS altimeter and the SRAD flight computer.

Open `camcontrol.kicad_pro` in KiCad 10. The board is a 5.72 in (145.3 mm) round, 2-layer disc
for the AV bay, placed and fully routed.

**Status (v16, 6 Oct 2026):** ERC 0 errors · DRC 0 violations with full schematic parity ·
`tools/layoutA/verify_A.py` ALL PASS. Ready to order: see [Ordering](#ordering).
[`LAYOUT_NOTES.md`](LAYOUT_NOTES.md) has the history of every layout decision.

---

## What's on it

| Block | Parts |
|---|---|
| 2S pack for camera + ESP32 | BT1, BT2 in series → 7.4 V nom / 8.4 V max |
| Input protection | F1 2 A polyfuse → SW1 (camera power switch plug) → D3 Schottky reverse-polarity diode → D1 SMBJ12A TVS |
| Buck 8.4 V → 5.0 V | U1 LMR51430 + L1 + FB divider |
| ESP32-DevKitC V4 socket | J1, J2 — 2 × 1×19 female headers |
| Camera harness | J3 — JST GH 5-pin (+5V, GND, RX, TX, VIDEO), on the back |
| Camera mount | H7–H10 — four M2 × 5 mm SMT standoffs on a 25.5 mm square, on the back |
| Status LED | R6 + D2 on GPIO2 |
| Pack voltage telemetry | R4/R5 divider + C8 → GPIO34 |
| COTS supply | BT3 → SW2 (COTS pin switch plug) → J5 Micro-Fit to the TeleMetrum |
| SRAD supply | BT4 → SW3 (SRAD pin switch plug) → J6 JST XH to the Aerolotl |

Harness connectors are latching Molex Micro-Fit 3.0 (SW1–SW3, J5) and JST GH (J3), per the
design review. J6 is a JST XH at the team's request to match the Aerolotl harness; it is
friction-fit, so secure the plug in flight.

---

## Three design decisions worth knowing

### 1. The Split 4 has no GPIO shutter line

Its harness is **VCC / GND / Video**. Recording start/stop is done over **UART**
using the RunCam Device Protocol on the TX/RX pads, not a single logic pin.

So the schematic wires **UART2** (GPIO17 TX, GPIO16 RX) to the camera through
100 Ω series resistors. UART0 is left free so you can still program and debug
over USB.

The camera connects to this board through the 5-pin J3 harness only (no
button-pad wiring).

### 2. Everything runs off one 5 V buck

The camera accepts 5–20 V, so 2S could feed it directly — but RunCam explicitly
warns to power it from a regulator rather than a raw battery bus.

Feeding the ESP32 8.4 V directly would also be a problem: the devkit's onboard
AMS1117 would drop 8.4 → 3.3 V and burn about **1.3 W** in a SOT-223. It would
run very hot.

One LMR51430 at 5 V solves both. The ESP32's regulator then only drops 5 → 3.3 V,
and the camera gets a clean supply.

Feedback divider: `Vout = 0.6 × (1 + 100k / 13k7) = 4.98 V`

### 3. COTS and SRAD grounds are deliberately isolated

`COTS_BAT-` and `SRAD_BAT-` are **not** tied to `GND`.

DTEG §6.9.1 requires completely independent recovery systems — separate power
supplies included. Tying the returns together would create a shared failure path
and defeat that. Each of those two cells is its own island: own cell, own switch,
own two-wire output.

Do not "clean this up" by merging the grounds.

---

## ESP32 pin map

| Function | Pin | Net |
|---|---|---|
| 5 V in | J1-19 | `+5V` |
| GND | J1-14, J2-1, J2-7 | `GND` |
| Camera UART TX | J2-11 (GPIO17) | `ESP_TX2` → R7 → `CAM_RX` |
| Camera UART RX | J2-12 (GPIO16) | `ESP_RX2` → R8 → `CAM_TX` |
| Status LED | J2-15 (GPIO2) | `LED_GPIO` → R6 → D2 |
| Pack voltage | J1-5 (GPIO34, ADC1) | `VBAT_SENSE` |

J1 is the devkit's left header (3V3 … 5V) and J2 the right header (GND … CLK),
both counted from the **antenna end**, which faces the top of the board.

Every unused header pin is broken out to a named net (`L06_IO35`, `R09_IO18`, …)
so you can see what's free. Those produce 31 `isolated_pin_label` ERC warnings —
expected and harmless, they're spare breakouts by design.

**GPIO6–11 (`IO6`…`IO11`) are wired to the module's SPI flash. Do not use them.**

---

## Camera mounting

The RunCam Split 4 board (29 × 29 mm, M2 holes on a 25.5 mm square) sits on four Würth
9774050243 M2 × 5 mm SMT standoffs (H7–H10) on the back of this board, next to its J3 harness.
`camcontrol.pretty/RunCam_Split4_OnStandoffs.kicad_mod` places its 3D outline; it has no pads
and is excluded from the BOM.

Source: [RunCam Split 4 manual](https://www.runcam.com/download/split4k/RC_Split_4k_Manual_EN.pdf)

---

## Open items

1. **The ESP32's Bluetooth is a 2.4 GHz transmitter.** DTEG §4.3.5 forbids
   powering transmitting electronics in the pit area without authorization, and
   2.4 GHz is not in ESRA's Student Band Plan. SW1 exists partly so you can keep
   it off until the pad. Declare this radio in your progress reports.
2. **No SD card module** is on this schematic — you mentioned one for the plate
   but didn't list it in the brief. Easy to add on SPI (GPIO5/18/19/23).
3. **Confirm the camera's logic level.** Most RunCam UART pads are 3.3 V, which
   matches the ESP32 directly. If yours is 5 V, add a level shifter — the 100 Ω
   series resistors are protection, not translation.

Layout-specific items are in [`LAYOUT_NOTES.md`](LAYOUT_NOTES.md).

---

## Ordering

Everything to order is in `fab/`:

| File | What it is |
|---|---|
| `fab/camcontrol_BOM.csv` | Ordering BOM: every soldered part with manufacturer + MPN (paste the MPNs into the DigiKey or Mouser BOM tool), plus the camera standoffs, plug-in modules, cells, cable-side connectors and the PCB. "Order qty" covers 2 boards plus spares. |
| `fab/camcontrol_gerbers.zip` | Gerbers + drill file. Upload as-is to JLCPCB (or any fab): 2 layers, 1.6 mm FR-4, 1 oz copper. |
| `fab/camcontrol_schematic.pdf` | The schematic, for review and for soldering. |

`cad/camcontrol_power_pcb.step` is the board with all parts for CAD.
`cad/avbay1_board_and_pin_switch_stack.step` is the board plus the exact pin-switch stack,
raised 18 mm into the Onshape stack frame; it is what the SSI AVBay1 Onshape document imports.

---

## Rebuilding

The layout is generated by scripts so it can be rebuilt after a change. Close KiCad first
(it rewrites project files when it quits), and use KiCad 10 on macOS (the scripts call its
bundled Python and `kicad-cli`).

```
tools/layoutA/build_A.sh /tmp/new.kicad_pcb   # place, route, labels, fields, refill, DRC, verify
cp /tmp/new.kicad_pcb camcontrol.kicad_pcb
python3 tools/annotate_mpn.py                 # after changing a part: edit PARTS in it first
python3 tools/make_bom.py                     # rewrites fab/camcontrol_BOM.csv
```

`tools/layoutA/` starts from `seed_user_1224.kicad_pcb`, the hand-placed version, so hand edits
to `camcontrol.kicad_pcb` are lost on the next rebuild: make changes in the scripts instead.
`tools/kc.py` holds the shared dimensions (disc size, battery and connector offsets). The one-shot
generators that made the very first versions are archived in `tools/obsolete/`; don't re-run them.

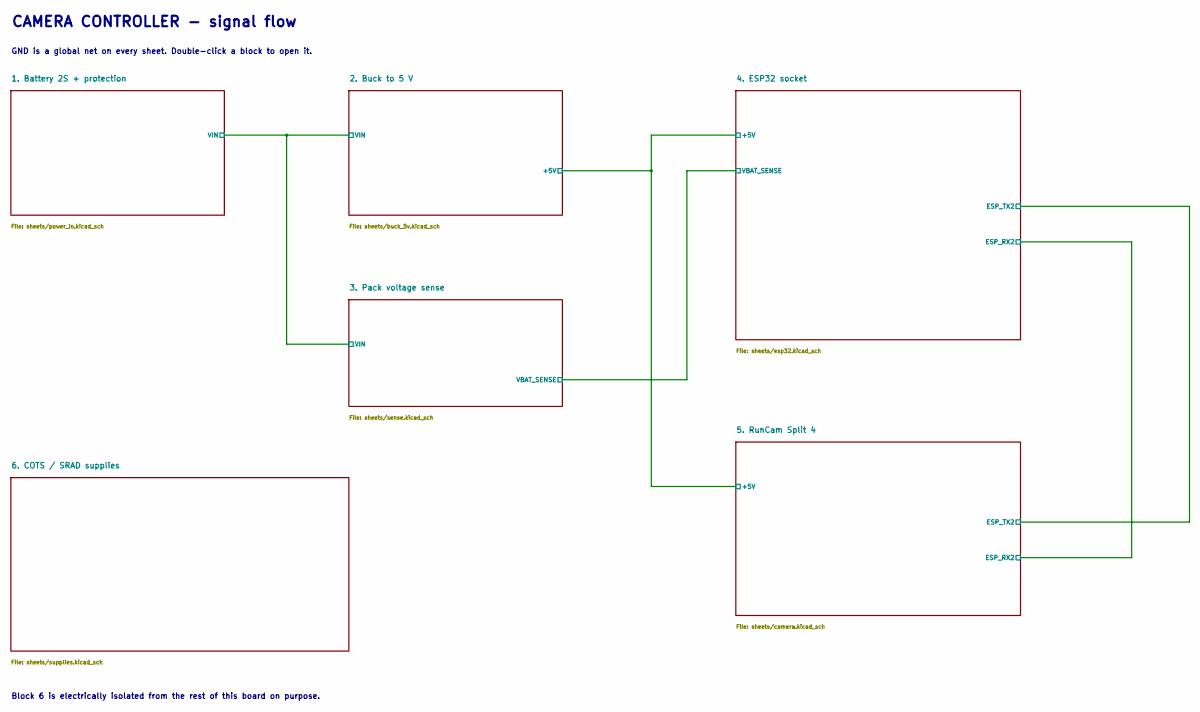
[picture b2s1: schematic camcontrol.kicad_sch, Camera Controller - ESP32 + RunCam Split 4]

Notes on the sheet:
CAMERA CONTROLLER - signal flow
GND is a global net on every sheet. Double-click a block to open it.
Block 6 is electrically isolated from the rest of this board on purpose.
